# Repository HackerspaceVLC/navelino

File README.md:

# navelino

Arduino custom para Hackerspace Valencia!
* ATMEGA328P-AU
* 3.3V
* 12Mhz

## Bootloader

Usamos una versión especial de optiboot compilada para 12Mhz.
Navelino con el Optiboot es el equivalente a un Arduino Uno

#### Optiboot

https://github.com/Optiboot/optiboot
https://github.com/Optiboot/optiboot/wiki/HowOptibootWorks

### Flashear el Bootloader

##### Buspirate:

Es posible usar el Buspirate como un ISP, hay que seguir las instrucciones del sisguiente enlace para conectar el Buspirate a los pines de ISP ( La versión de Buspirate es importante )

http://dangerousprototypes.com/docs/Bus_Pirate_AVR_Programming
http://dangerousprototypes.com/docs/Bus_Pirate_I/O_Pin_Descriptions
https://antibore.files.wordpress.com/2011/06/buspirate.png

#### Linux & Mac

```
avrdude -c buspirate -P /dev/<device> -p atmega328p -U flash:w:optiboot_atmega328_12.hex -U lfuse:w:0xFF:m -U hfuse:w:0xDE:m -U efuse:w:0x05:m
```

#### Windows

???

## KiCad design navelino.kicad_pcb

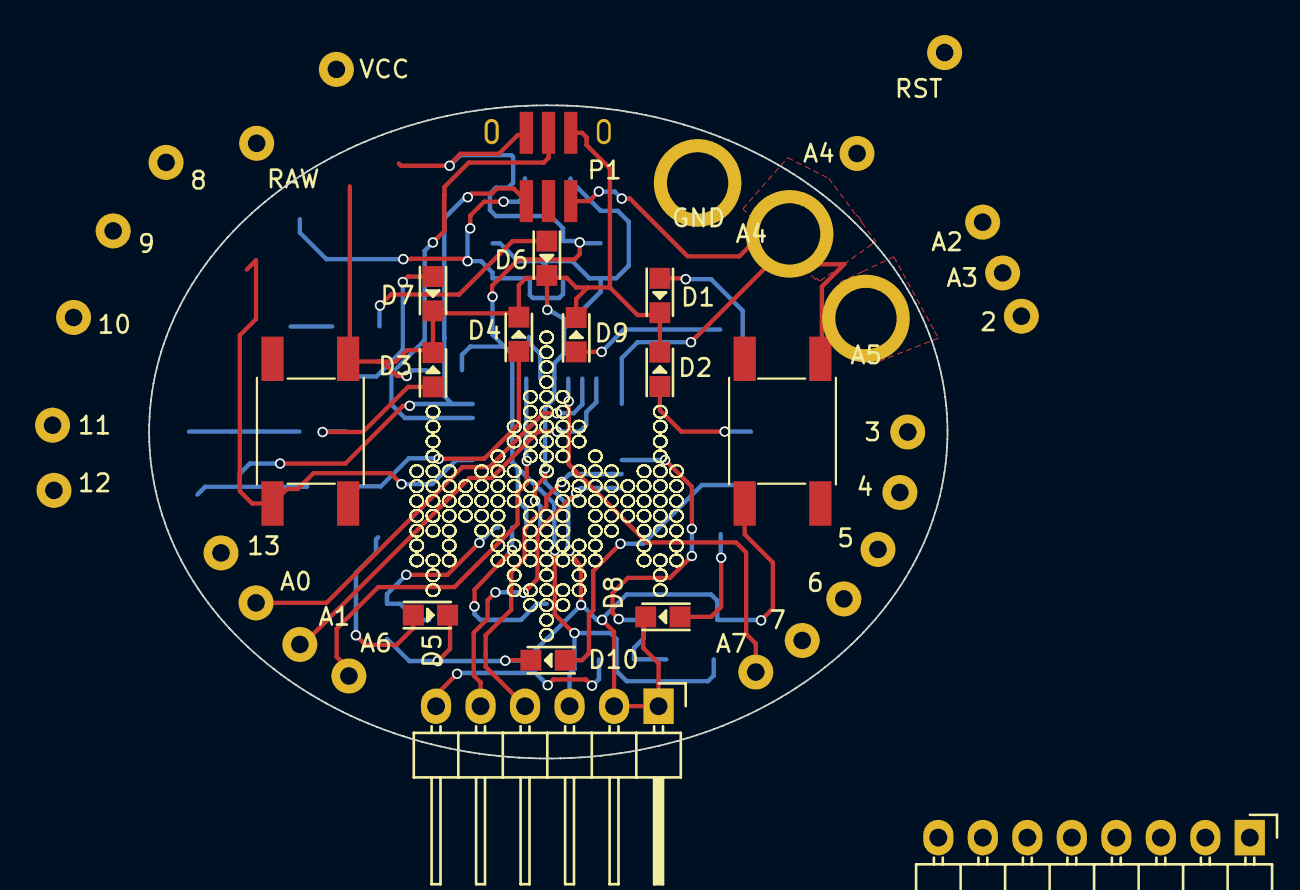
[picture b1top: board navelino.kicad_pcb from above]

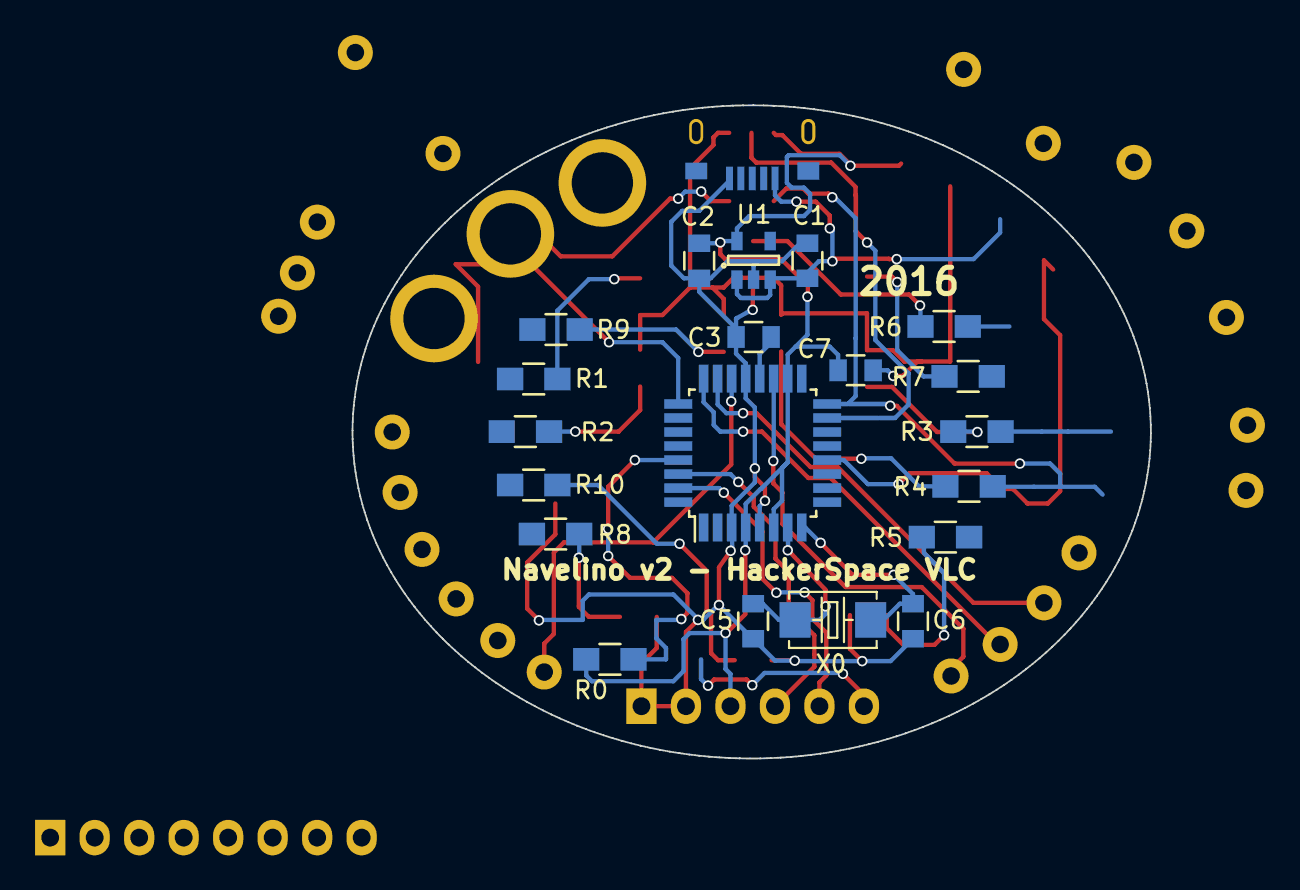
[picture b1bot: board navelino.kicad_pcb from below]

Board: 2 copper layers, 45.6 x 37.3 mm, 60 parts (21 on the bottom side), 39 nets.

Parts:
2, 3, 4, 5, 6, 7, 8, 9, 10, 11, 12, 13: CONN_1; SolderWirePad_single_1mmDrill
A0, A1, A2, A3, A4, A4#2, A5, A6, A7: CONN_1; SolderWirePad_single_1mmDrill
C1, C3, C7: 0.1uF; C_0805
C2: 1uF; C_0805
C5, C6: 27pF; C_0805
CON1: USB; ST-USB-001G
D1, D2, D3: BLUE; LED-0805
D4, D5, D6, D7, D8, D9, D10: LED; LED-0805
GND: CONN_1; SolderWirePad_single_1mmDrill
IC1: ATMEGA328P-A; TQFP-32_7x7mm_Pitch0.8mm
P1: CONN_02X03; ISPSMD
P3: CONN_6; Pin_Header_Angled_1x06
R0: 10K; R_0805_HandSoldering
R1, R2, R3, R4, R5, R6, R7, R8, R9, R10: 330; R_0805_HandSoldering
RAW: CONN_1; SolderWirePad_single_1mmDrill
RST: CONN_1; SolderWirePad_single_1mmDrill
SW1, SW2: SMD-SWITCH-TACTILE-SPST-NO(4P-D6.0MM); SW4-SMD-6.0X6.0X5.0MM
U1: XC6204B332MR; SOT-23-5
VCC: CONN_1; SolderWirePad_single_1mmDrill
X0: CRYSTAL; X2-SMD-5.0X3.2X1.3MM

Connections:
A6: A6.1, IC1.19
A7: A7.1, IC1.22
GND: C1.2, C2.2, C3.2, C5.1, C6.1, C7.2, CON1.5, D1.2, D2.2, D3.2, D4.2, D5.2, D6.2, D7.2, D8.2, D9.2, D10.2, GND.1, IC1.3, IC1.5, IC1.21, P1.6, P3.1, P3.2, SW1.3, SW2.3, U1.2
unnamed: C3.1, IC1.20
unnamed: D1.1, R1.2
unnamed: D2.1, R2.2
unnamed: D3.1, R3.2
unnamed: D4.1, R4.2
unnamed: D5.1, R5.2
unnamed: D6.1, R6.2
unnamed: D7.1, R7.2
unnamed: D8.1, R8.2
unnamed: D9.1, R9.2
unnamed: D10.1, R10.2
PB0: 8.1, IC1.12, SW2.1
PB1: 9.1, IC1.13
PB2: 10.1, IC1.14
PB3/MOSI: 11.1, IC1.15, P1.4
PB4/MISO: 12.1, IC1.16, P1.1
PB5/SCK: 13.1, IC1.17, P1.3
PC0: A0.1, IC1.23
PC1: A1.1, IC1.24
PC2: A2.1, IC1.25, SW1.1
PC3: A3.1, IC1.26
PD2: 2.1, IC1.32
PD3: 3.1, IC1.1
PD4: 4.1, IC1.2
PD5: 5.1, IC1.9
PD6: 6.1, IC1.10
PD7: 7.1, IC1.11
RAW: C1.1, CON1.1, RAW.1, U1.1, U1.3
RESET: IC1.29, P1.5, R0.1, RST.1
RXI: IC1.30, P3.4
SCL: A5.1, IC1.28
SDA: A4.1, A4#2.1, IC1.27
TXO: IC1.31, P3.5
VCC: C2.1, C7.1, IC1.4, IC1.6, IC1.18, P1.2, P3.3, R0.2, U1.5, VCC.1
XTAL1: C5.2, IC1.7, X0.1
XTAL2: C6.2, IC1.8, X0.2

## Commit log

2015-06-27 Import inicial
2015-06-28 Actualizado el regulador a algo más pequeño :)
2015-06-29 Eliminados los archivos bak
2015-10-13 Cambiados casi todos los componentes de 06 a 08 para que pueda funcionar como taller de soldadura SMD Añadido el Jumper para poder desactivar los leds y usar los pines libremente
2015-12-15 Finalizado el routing!
2015-12-18 Un poco de amor para el Silkscreen
2015-12-18 Cambios de algunas referencias de seeed
2015-12-21 Condensadores de X0 cambiados a 27pF Añadidos orificios de montaje de 3mm
2015-12-21 Pequeños ajustes antes de generar el gerber
2015-12-21 Versión con los Jumpers de los leds cerrados
2016-01-12 PDF con eschema actualizado
2016-02-15 Intercambio TX/RX
2016-02-15 Intercambio RX/TX Conexión GND que faltaba en etapa de alimentación
2016-02-16 Versión inicial de Navefire, prueba de leds / botones, etc
2016-02-16 boards.txt para poder programar desde Arduino
2016-02-27 Upssss, carga de librerías, BOM para SEED, y ZIP
2016-10-25 Empezando a meter las dependencias de librerías dentro del proyecto Substituido el conector de la hoja por algo más standard
2016-11-14 Archivos de fabricación de la v2
2016-11-14 Añadir información para cargar el bootloader desde buspirate
2016-11-14 Actualizar rev2 en el pdf
2016-11-14 Añadido bootloader Optiboot compilado para 12Mhz
2016-11-17 Add some Mac files to .gitignore
2016-11-21 Corregida la huella de los LEDs 0805, el cátodo ya está donde toca :)
2016-12-06 Empezando rev3
    - Permitir hojas intercambiables, conector SPI completo
    - Usar charlieplexing para reducir el numero de GPIOS para los leds a 4
    en vez de 10
    - Eliminar el botón de reset, se usara una pulsación prolongada de los
    dos botones de disparo para hacer un reset software
    - Añadir soporte V-USB en el cuerpo
2016-12-06 Casi finalizado el nuevo esquema
